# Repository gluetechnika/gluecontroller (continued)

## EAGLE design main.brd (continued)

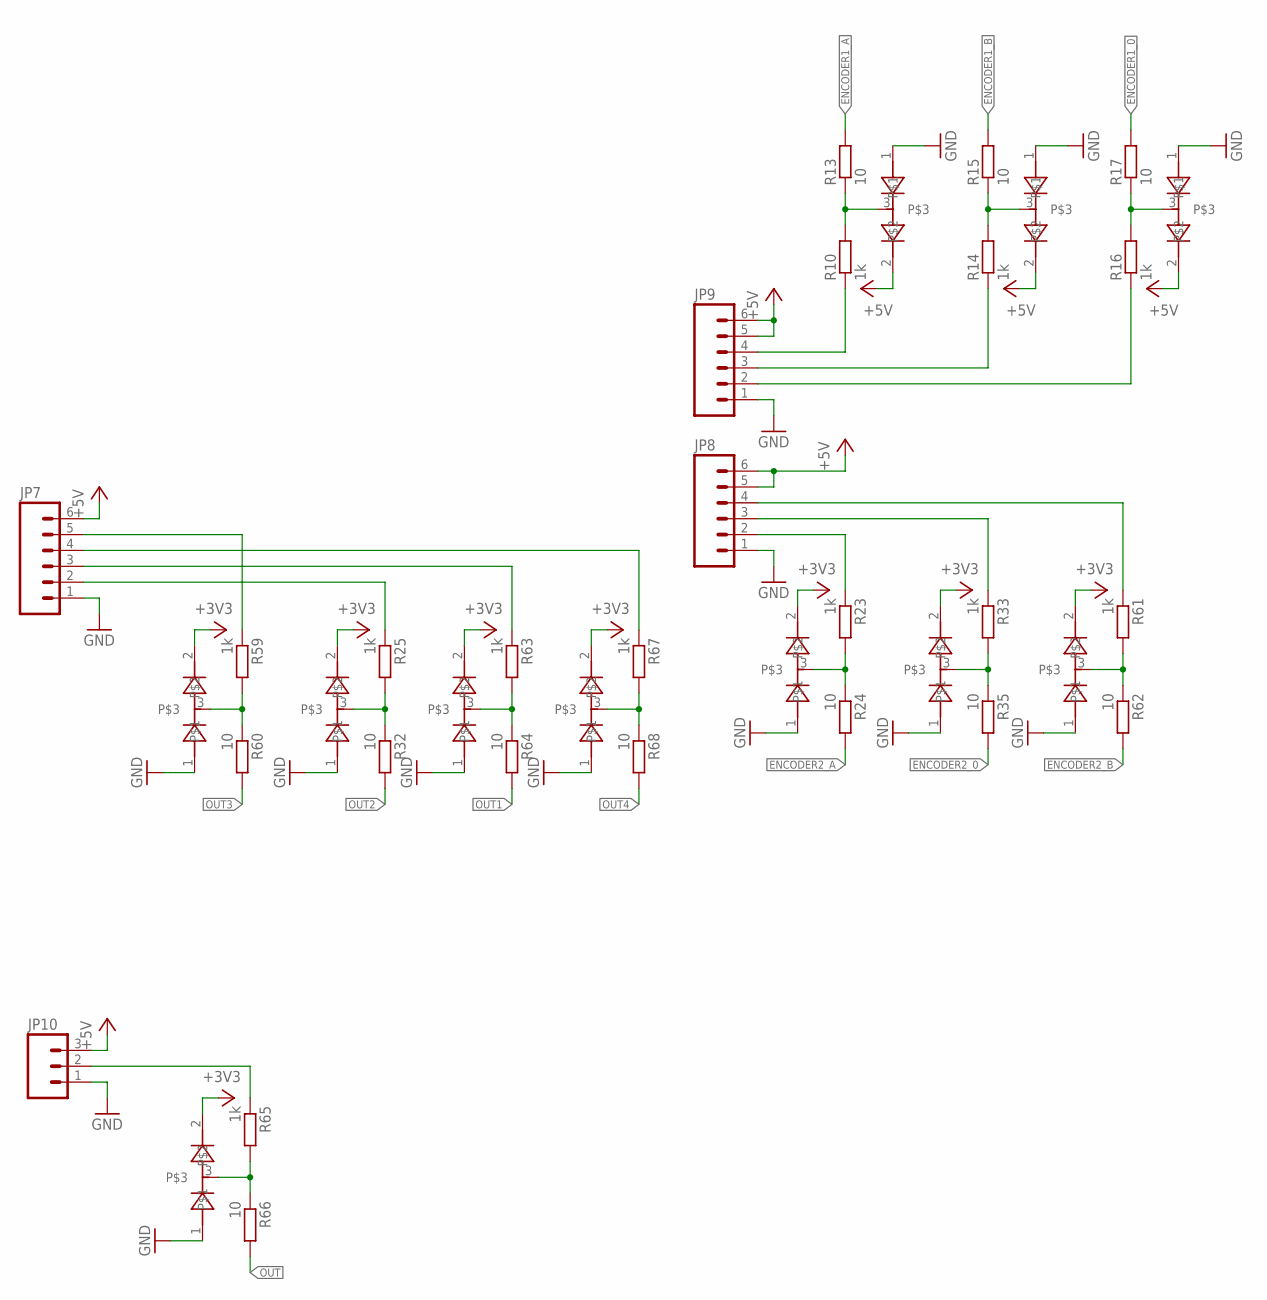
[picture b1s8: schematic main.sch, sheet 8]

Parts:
JP7, JP8, JP9: M063.5MM-6; SCREWTERMINAL-3.5MM-6
JP10: M03SCREW; SCREWTERMINAL-3.5MM-3
R10, R14, R16, R23, R25, R33, R59, R61, R63, R65, R67: 1k; R0603
R13, R15, R17, R24, R32, R35, R60, R62, R64, R66, R68: 10; R0603
U$6, U$8, U$9, U$10, U$11, U$12, U$13, U$14, U$15, U$16, U$17: BAS40W-04; SOT65P210X110-3N

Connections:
+3V3: U$10.2, U$11.2, U$12.2, U$13.2, U$14.2, U$15.2, U$16.2, U$17.2; also elsewhere on the board
+5V: JP7.6, JP8.5, JP8.6, JP9.5, JP9.6, JP10.3, U$6.2, U$8.2, U$9.2; also elsewhere on the board
ENCODER1_0: R17.2; also elsewhere on the board
ENCODER1_A: R13.2; also elsewhere on the board
ENCODER1_B: R15.2; also elsewhere on the board
ENCODER2_0: R35.2; also elsewhere on the board
ENCODER2_A: R24.2; also elsewhere on the board
ENCODER2_B: R62.2; also elsewhere on the board
GND: JP7.1, JP8.1, JP9.1, JP10.1, U$6.1, U$8.1, U$9.1, U$10.1, U$11.1, U$12.1, U$13.1, U$14.1, U$15.1, U$16.1, U$17.1; also elsewhere on the board
unnamed: JP8.2, R23.1
unnamed: JP8.3, R33.1
unnamed: JP7.5, R59.1
unnamed: R10.2, R13.1, U$6.3
unnamed: JP9.4, R10.1
unnamed: JP8.4, R61.1
unnamed: R16.2, R17.1, U$9.3
unnamed: R14.2, R15.1, U$8.3
unnamed: JP9.3, R14.1
unnamed: R25.2, R32.1, U$11.3
unnamed: JP9.2, R16.1
unnamed: R23.2, R24.1, U$10.3
unnamed: JP7.2, R25.1
unnamed: JP7.3, R63.1
unnamed: JP7.4, R67.1
unnamed: R65.2, R66.1, U$16.3
unnamed: JP10.2, R65.1
unnamed: R33.2, R35.1, U$12.3
unnamed: R59.2, R60.1, U$13.3
unnamed: R63.2, R64.1, U$15.3
unnamed: R61.2, R62.1, U$14.3
unnamed: R67.2, R68.1, U$17.3
OUT: R66.2; also elsewhere on the board
OUT1: R64.2; also elsewhere on the board
OUT2: R32.2; also elsewhere on the board
OUT3: R60.2; also elsewhere on the board
OUT4: R68.2; also elsewhere on the board

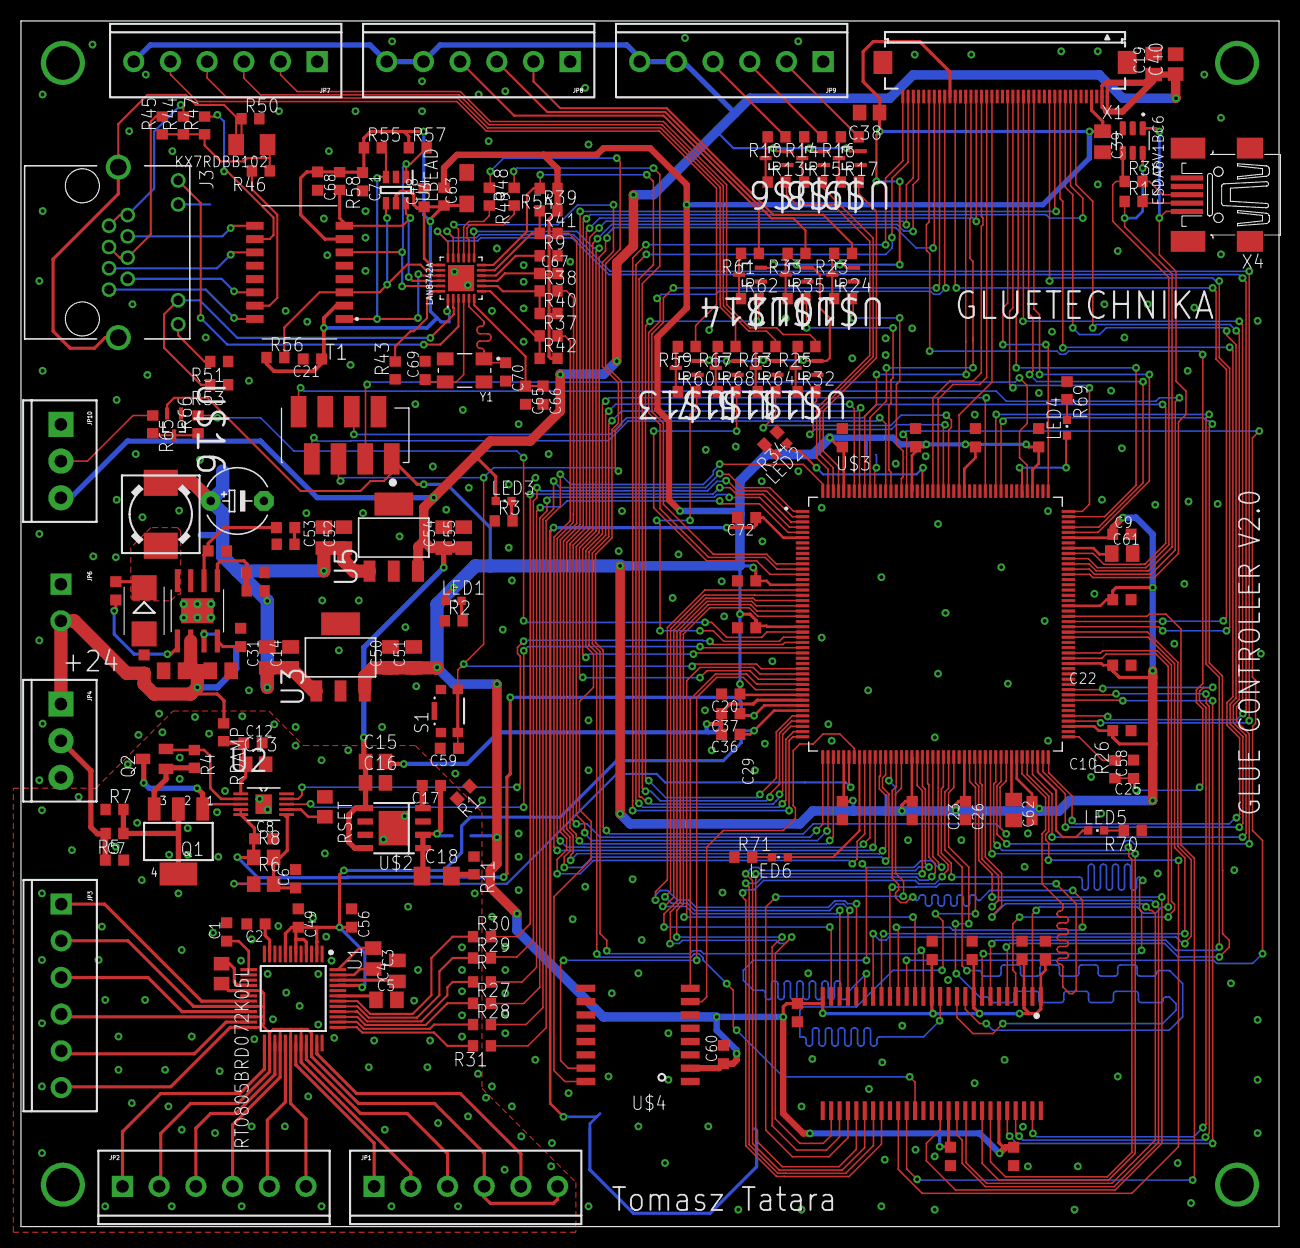
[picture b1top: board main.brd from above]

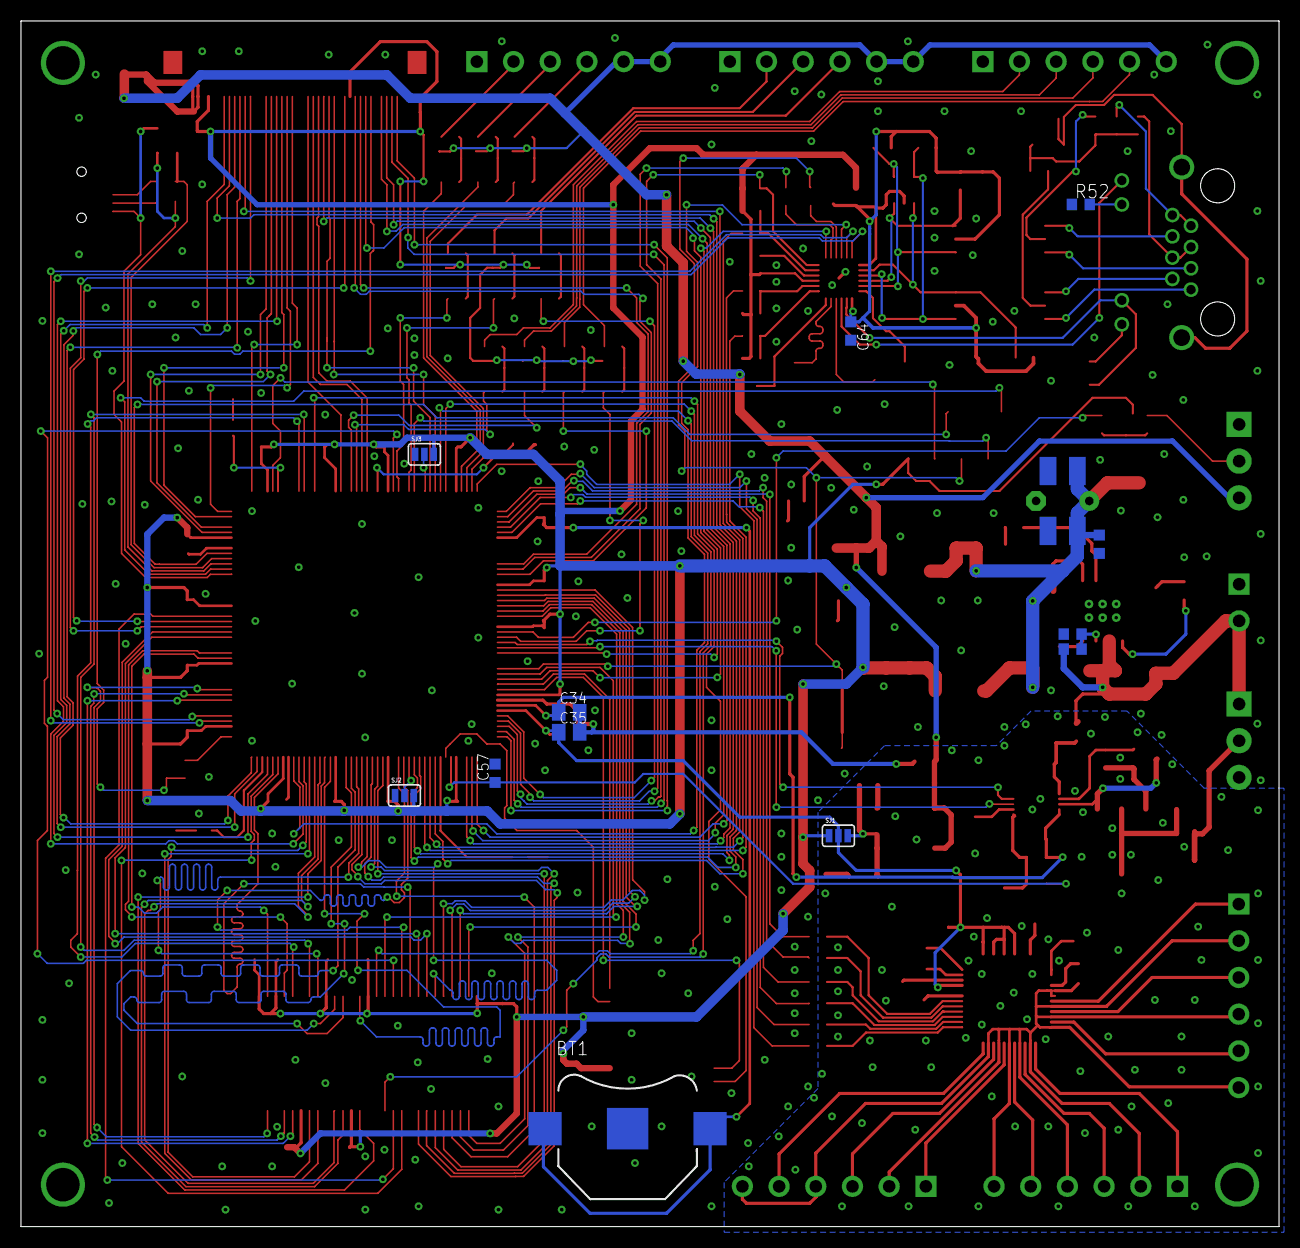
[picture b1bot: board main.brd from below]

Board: 2 copper layers, 120.0 x 115.0 mm, 213 parts (14 on the bottom side), 224 nets.
